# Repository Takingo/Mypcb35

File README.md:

# OmniCircuit AI

OmniCircuit AI is a local proof of concept for an autonomous PCB/PCBA design and manufacturing suite. The current implementation focuses on the ESP32-S3 + DWM3000 UWB Anchor example and establishes the architecture for:

- Parsing structured schematic, BOM, and PCB constraint inputs.
- Running deterministic engineering checks for RF, isolation, power, level shifting, expansion, and testability requirements.
- Producing AI design, validation, and manufacturing handoff reports.
- Presenting the project state in a Flutter dashboard.

The referenced `Corning-AI/PCBai` repository currently presents a public roadmap-style README for conversational PCB design, placement, routing, DRC, SI, and Gerber export. This workspace therefore treats PCBai as a planned adapter boundary while the local proof of concept supplies deterministic parsers and validators that can be connected to PCBai or KiCad automation later.

## Run the Local Engine

```powershell
python -m engine.run_pipeline --project-root .
```

Generated files are written to `outputs/uwb_anchor/` and the dashboard asset is written to `assets/generated/uwb_anchor_analysis.json`.

## Run the Flutter Dashboard

```powershell
C:\flutter\bin\flutter.bat pub get
C:\flutter\bin\flutter.bat run -d chrome
```

The input panel supports both manual text entry and file import. Use `Ister Dosyasi`, `BOM Yukle`, or `Teknik Not` to load text-based design inputs such as `.md`, `.csv`, `.txt`, `.json`, `.net`, `.xml`, `.yaml`, `.sch`, or `.kicad_sch` files directly into the matching field. On Windows desktop you can either browse with `Gozat` or paste a path such as `C:\Mypcb\BOM.csv` and press `Yoldan Yukle`.

## Project Layout

- `SCHEMATIC.md`, `BOM.csv`, `PCB_NOTES.md`: UWB anchor input package.
- `engine/`: Python proof-of-concept engine, including the Phase 2 KiCad automation bridge.
- `lib/`: Flutter dashboard.
- `assets/generated/`: Engine output consumed by Flutter.
- `outputs/`: Reports and manufacturing handoff placeholders.

## Phase 2 KiCad Bridge

The KiCad bridge lives in `engine/kicad_automation_service.py`. It reads `AI_Netlist_v1`, creates KiCad project artifacts, injects RF and AC safety constraints, and can run headless `kicad-cli` DRC/Gerber/drill/CPL exports when KiCad is installed.

```powershell
python -m engine.kicad_automation_service --netlist outputs/phase1/AI_NETLIST_V1.example.json --output-root outputs/kicad
```

On this Windows workspace with KiCad 10 installed, use the wrapper script:

```powershell
.\tool\run_kicad_phase2.ps1 -Export
```

For automation testing only, exports can be forced despite DRC violations:

```powershell
.\tool\run_kicad_phase2.ps1 -Export -ContinueOnDrcError
```

## Phase 3 DRC Feedback

KiCad DRC JSON can be normalized into `DRC_REPORT_V1` and converted into PCBai-style optimization penalties:

```powershell
& "C:\Program Files\KiCad\10.0\bin\python.exe" -m engine.drc_parser `
  --input outputs\kicad\esp32_s3_dwm3000_uwb_anchor_with_relay_outputs\manufacturing\drc_report.json `
  --output outputs\phase3\DRC_REPORT_V1.json
```

The Flutter dashboard includes a `DRC` tab that reads `assets/generated/drc_report_v1.json`.

## Phase 4 Closed-Loop Layout Optimization

The layout optimizer reads normalized DRC feedback, applies conservative `pcbnew` repairs, reruns DRC, and exports manufacturing files only when the final DRC count is zero.

```powershell
.\tool\run_layout_optimizer.ps1
```

Generated status:

- `outputs/phase4/layout_optimization_status.json`
- `outputs/phase4/gerber/`
- `outputs/phase4/drill/`
- `outputs/phase4/position/pick_and_place.csv`

Current KiCad status for the UWB anchor proof of concept:

- Schematic ERC: `0` violations.
- PCB DRC: `0` violations after closed-loop optimizer.
- Manufacturing exports: Gerber, drill, and pick-and-place generated.

## Simulation and PCBA Evidence

Run deterministic first-order engineering checks:

```powershell
.\tool\run_simulation_checks.ps1
```

Run assembly/PCBA visual exports:

```powershell
.\tool\run_pcba_exports.ps1
```

Generated files include:

- `outputs/simulation/simulation_report.json`
- `outputs/simulation/simulation_report.md`
- `outputs/assembly/*.pdf`
- `outputs/assembly/*.svg`
- `outputs/assembly/pcba_preview.glb`

## Fabrication Package

Create the local PCBWay/JLCPCB-style production archive and quote estimate:

```powershell
.\tool\run_fabrication_package.ps1
```

Generated package:

- `outputs/fabrication/Quantum_Mind_Anchor_v2_4_Production.zip`

## Engineering Readiness Gate

DRC=0 is not enough to claim a real production-ready electronic design. Run the engineering audit to verify schematic symbols/ERC evidence, active PCB consistency, simulation evidence, PCBA handoff files, and fabrication package integrity.

```powershell
.\tool\run_engineering_audit.ps1
```

Generated files:

- `outputs/engineering/engineering_readiness_report.json`
- `assets/generated/engineering_readiness_report.json`

Latest local audit result:

- `overall_status`: `review_required`
- `readiness_percent`: `86`
- blockers: `0`
- review warnings: `1` simulation/stackup review item

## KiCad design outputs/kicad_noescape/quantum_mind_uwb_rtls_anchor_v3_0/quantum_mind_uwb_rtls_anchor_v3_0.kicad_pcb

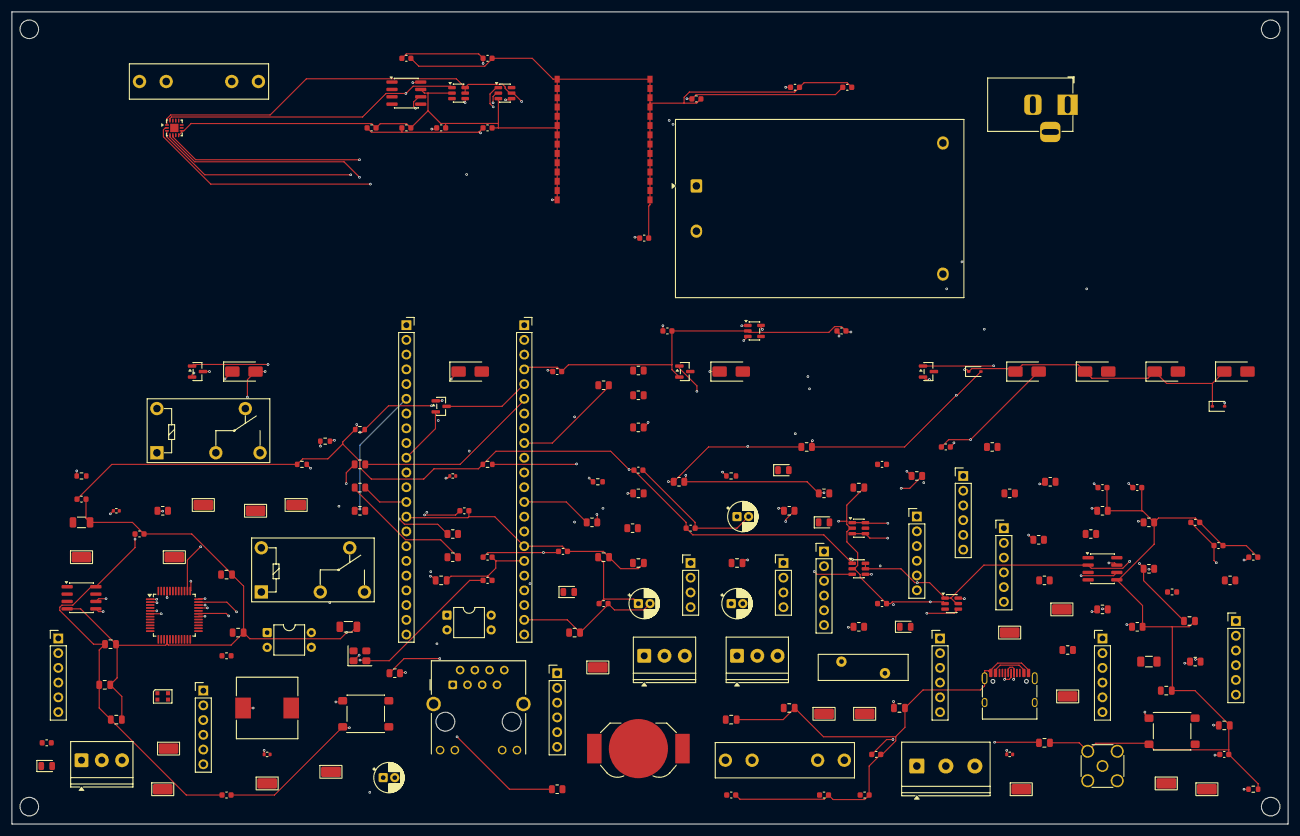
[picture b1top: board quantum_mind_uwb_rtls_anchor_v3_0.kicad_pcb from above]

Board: 4 copper layers, 220.0 x 140.0 mm, 195 parts (0 on the bottom side), 65 nets.

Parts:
ANT1: SMA Female Edge Mount 50Ω; SMA_Amphenol_132134_Vertical
BAT1: CR2032 Holder SMD; BatteryHolder_LINX_BAT-HLD-012-SMT
C1, C2, C3, C4: 10µF/50V Electrolytic; CP_Radial_D5.0mm_P2.00mm
C5, C6, C7, C8, C9, C10, C11, C12: 100nF/50V X7R 0805; C_0805_2012Metric
C13, C14, C15, C16: 10µF/16V X5R 0805; C_0805_2012Metric
C17, C18, C19, C20: 1µF/16V X7R 0603; C_0603_1608Metric
C21, C22: 22µF/10V X5R 1206; C_1206_3216Metric
C23, C24: 4.7µF/50V X7R 0805; C_0805_2012Metric
C25, C26: 10µF/6.3V X5R 0805; C_0805_2012Metric
C27, C28, C29, C30, C33, C34, C35, C36, C37, C38: 100nF/16V X7R 0603; C_0603_1608Metric
C31: 330pF/50V C0G 0603; C_0603_1608Metric
C32: 100pF/50V C0G 0603; C_0603_1608Metric
C39, C40, C41, C42: 100nF/50V X7R 0603; C_0603_1608Metric
C43, C44: 10µF/25V X5R 0805; C_0805_2012Metric
C90, C91, C92, C93, C94, C95, C96, C97, C98, C99, C100, C101, C102: 100nF; C_0603_1608Metric
C_X1A, C_X1A-C_X1B, C_X1B: 18pF/50V C0G 0603; C_0603_1608Metric
D1: SS34-E3/57T; D_SMA
D2, D3: 1N5819; D_SMA
D4, D5: 1N4148TR; D_SOD-323
D6, D7, D8: SMBJ3.3A; D_SMA
D9: SMBJ1.8A; D_SMA
D10: USBLC6-2SC6; SOT-23-6
F1: 0215001.MXP; Fuseholder_Littelfuse_100_series_5x20mm
F2: 0ZCJ0050FF2G; Fuse_1206_3216Metric
FB1, FB2, FB3: BLM18PG221SN1D; L_0603_1608Metric
J1_AC: Screw Terminal 3-pin 5.0mm; TerminalBlock_Phoenix_PT-1,5-3-5.0-H_1x03_P5.00mm_Horizontal
J1_USB: USB Type-C Receptacle 16-pin; USB_C_Receptacle_HRO_TYPE-C-31-M-12
J2: DC Power Jack 5.5×2.1mm; BarrelJack_Horizontal
J3, J4, J5: Screw Terminal 3-pin 3.5mm; TerminalBlock_Phoenix_PT-1,5-3-3.5-H_1x03_P3.50mm_Horizontal
J6, J7, J8, J9, J10, J11, J12, J13, J16, J17: Pin Header 1×6 2.54mm Male; PinHeader_1x06_P2.54mm_Vertical
J14, J15: Pin Header 1×4 2.54mm Male; PinHeader_1x04_P2.54mm_Vertical
J18: HR911105A; RJ45_Hanrun_HR911105A_Horizontal
J_FUSE: Fuse Holder 5×20mm PCB; Fuseholder_Littelfuse_100_series_5x20mm
K1, K2: G5Q-14-DC5; Relay_SPDT_Omron-G5Q-1
L1: CDRH104R-220NC; L_10.4x10.4_H4.8
LED1, LED5: Green LED 0805; LED_0805_2012Metric
LED2: Blue LED 0805; LED_0805_2012Metric
LED3: Red LED 0805; LED_0805_2012Metric
LED4: Yellow LED 0805; LED_0805_2012Metric
LED6: WS2812B-2020; LED_WS2812B-2020_PLCC4_2.0x2.0mm
Q1, Q2, Q3, Q4: 2N7002; SOT-23
R1, R1-R3R_LED4R_LED5, R2, R3: 220Ω 0805 1/4W; R_0805_2012Metric
R6, R7, R8, R9, R18, R19, R28, R29, R30, R34: 10kΩ 0805 1/4W; R_0805_2012Metric
R10, R11, R41, R42: 1kΩ 0805 1/4W; R_0805_2012Metric
R12, R13: 4.7kΩ 0805 1/4W; R_0805_2012Metric
R14: 10kΩ 0805 1%; R_0805_2012Metric
R15: 31.6kΩ 0805 1%; R_0805_2012Metric
R16, R17: 330Ω 0805 1/4W; R_0805_2012Metric
R20, R21, R22, R23, R31, R32: 100Ω 0805 1/4W; R_0805_2012Metric
R33: 0Ω 0805; R_0805_2012Metric
R35, R36, R37: 10kΩ 0603 1/8W; R_0603_1608Metric
R38, R39, R40: 100Ω 0603 1/8W; R_0603_1608Metric
R43, R44, R45, R46: 49.9Ω 0402 1%; R_0402_1005Metric
R47: 470Ω 0805 1/4W; R_0805_2012Metric
RV1: 14D471K; RV_Disc_D15.5mm_W4.5mm_P7.5mm
R_LED4, R_LED5: 220Ω 0805 1/4W; R_0805_2012Metric
R_RST1, R_RST2: 10kΩ 0603 1/8W; R_0603_1608Metric
R_WDG: 100kΩ 0805 1/4W; R_0805_2012Metric
SK1, SK2: PinSocket_1x22_P2.54mm; PinSocket_1x22_P2.54mm_Vertical
SW1, SW2: Tactile Switch 6×6mm SMD; SW_SPST_PTS645Sx43SMTR92
TP1, TP2, TP3, TP4, TP5, TP6, TP7, TP8, TP9, TP10, TP11, TP12, TP13, TP14, TP15, TP16, TP17, TP18: Test Point SMD 1.27mm Red; TestPoint_Keystone_5015_Micro_Mini
U2: DWM3000
U3: HLK-10M05; Converter_ACDC_Hi-Link_HLK-10Mxx
U4: TPS54331DR; SOIC-8_3.9x4.9mm_P1.27mm
U5: TPS780180200DRV; SOT-23-5
U6: TXB0104RGYR; WQFN-14-1EP_2.5x2.5mm_P0.5mm_EP1.45x1.45mm
U7, U13, U14: SN74LVC1T45DBVR; SOT-23-6
U8: TPL5010DDCR; SOT-23-6
U9: DS3231SN; SOIC-8_3.9x4.9mm_P1.27mm
U10: AT24C256C-SSHL; SOIC-8_3.9x4.9mm_P1.27mm
U11, U12: PC817X2CSP9F; DIP-4_W7.62mm
U15: W5500; LQFP-48_7x7mm_P0.5mm
X1: 25MHz / 18pF; Crystal_SMD_3225-4Pin_3.2x2.5mm

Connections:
1V8_DWM: C17.1, C18.1, C19.1, C20.1, C27.1, C28.1, C30.1, C33.1, C35.1, C38.1, D9.2, R35.1, R36.1, R37.1, U5.3, U6.14, U7.1, U13.1, U14.6
3V3_MAIN: C3.1, C4.1, C6.1, C7.1, C8.1, C9.1, C10.1, C23.1, C24.1, C29.1, C34.1, C36.1, C37.1, R28.1, R29.1, R30.1, R34.1, U5.1, U6.1, U7.5, U7.6, U8.5, U9.2, U10.8, U13.5, U13.6, U14.1, U14.5
5V_MAIN: C1.1, C2.1
5V_USB: J1_USB.A4, J1_USB.A9, J1_USB.B4, J1_USB.B9
5V_USB_FILTERED: SK1.1, SK2.1
+1V8: C92.1, C94.1, C96.1, C98.1, C102.1
+3V3: C90.1, C91.1, C93.1, C95.1, C97.1, C100.1, C101.1
+5V_ISO: C99.1, D1.1, D2.1, D3.1, D4.1, D5.1, D6.1, D7.1, D8.1, D9.1, K1.1, K2.1
AC_L: J1_AC.1, RV1.1, U3.1
AC_N: J1_AC.2, RV1.2, U3.2
GND: ANT1.2, C1.2, C2.2, C3.2, C4.2, C5.2, C6.2, C7.2, C8.2, C9.2, C10.2, C11.2, C12.2, C13.2, C14.2, C15.2, C16.2, C17.2, C18.2, C19.2, C20.2, C21.2, C22.2, C23.2, C24.2, C25.2, C26.2, C27.2, C28.2, C29.2, C30.2, C31.2, C32.2, C33.2, C34.2, C35.2, C36.2, C37.2, C38.2, C39.2, C40.2, C41.2, C42.2, C43.2, C44.2, C90.2, C91.2, C92.2, C93.2, C94.2, C95.2, C96.2, C97.2, C98.2, C99.2, C100.2, C101.2, C102.2, C_X1A.2, C_X1B.2, D10.2, J1_USB.A1, J1_USB.A12, J1_USB.B1, J1_USB.B12, J1_USB.SH, J2.2, J2.3, J18.SH, Q1.2, Q2.2, Q3.2, Q4.2, R14.2, R18.2, R19.2, R_RST2.2, R_WDG.2, SK1.2, SK1.10, SK1.11, SK1.13, SK1.14, SK2.2, SK2.3, SK2.4, SK2.16, SK2.17, SK2.18, SK2.19, SK2.20, SK2.21, SK2.22, SW1.2, SW2.2, U2.1, U2.2, U2.3, U2.4, U2.5, U2.6, U2.7, U2.8, U2.9, U2.10, U2.11, U2.12, U2.13, U2.14, U2.15, U2.16, U2.17, U2.18, U2.19, U2.20, U2.21, U2.22, U2.23, U2.24, U2.25, U2.26, U2.27, U2.28, U3.4, U4.7, U5.2, U6.7, U6.8, U7.2, U8.3, U9.5, U10.4, U13.2, U14.2, U15.16
NET_DWM3000_DEBUGOUT_1V8: R37.2, R40.1
NET_DWM3000_EXT_RX_1V8: R35.2, U14.4
NET_DWM3000_EXT_TX_1V8_SERIES: R36.2, R39.1, U13.3
NET_DWM3000_RSTN_1V65: R_RST1.2, R_RST2.1
NET_DWM3000_SPI_CLK_3V3_SERIES: R20.2, U6.2
NET_DWM3000_SPI_CS_3V3_SERIES: R23.2, U6.5
NET_DWM3000_SPI_MISO_3V3_SERIES: R22.2, U6.4
NET_DWM3000_SPI_MOSI_3V3_SERIES: R21.2, U6.3
NET_ESP32_EN: D5.2, Q1.3, R28.2, R47.1, SK1.3, SW1.1, U8.4
NET_ESP32_EXT_RX: R38.1, SK1.9
NET_ESP32_EXT_TX: SK1.8, U13.4
NET_ESP32_GPIO0: D4.2, Q2.3, R29.2, SK2.5, SW2.1
NET_ESP32_GPIO1: R_LED4.1, SK1.17
NET_ESP32_GPIO2: R_LED5.1, SK1.18
NET_ESP32_GPIO4: R16.1, SK1.4
NET_ESP32_GPIO5: R17.1, SK1.5
NET_ESP32_GPIO6: R2.1, SK1.6
NET_ESP32_GPIO7: R3.1, SK1.7
NET_ESP32_GPIO8: C11.1, SK1.12
NET_ESP32_GPIO9: R_RST1.1, SK2.15
NET_ESP32_GPIO45: R30.2, SK2.6, U8.2
NET_ESP32_IRQ: SK2.10, U7.4
NET_ESP32_SPI_CLK: R20.1, SK2.14
NET_ESP32_SPI_CS: R23.1, SK2.11
NET_ESP32_SPI_MISO: R22.1, SK2.12
NET_ESP32_SPI_MOSI: R21.1, SK2.13
NET_I2C_SCL: R13.2, U9.7, U10.6
NET_I2C_SDA: R12.2, SK2.9, U9.6, U10.5
NET_U4_COMP: C31.1, C32.1, U4.6
NET_U4_FB: R14.1, R15.2
NET_U4_SW: D1.2, L1.1, U4.8
NET_U5_EN: R34.2, U5.5
NET_U8_DELAY: R_WDG.1, U8.1
NET_U11_COLLECTOR: Q3.1, R18.1
NET_U12_COLLECTOR: Q4.1, R19.1
NET_USB_DTR: Q1.1, R31.1
NET_USB_D_N: D10.3, D10.4, J1_USB.A7, J1_USB.B7
NET_USB_D_P: D10.1, D10.6, J1_USB.A6, J1_USB.B6
NET_USB_RTS: Q2.1, R32.1
NET_W5500_INT: R42.1, SK2.7
NET_W5500_INTn: R42.2, U15.38
NET_W5500_REGD: C44.1, U15.45
NET_W5500_RST: R41.1, SK2.8
NET_W5500_RX_N: J18.6, R46.1, U15.6
NET_W5500_RX_P: J18.3, R45.1, U15.5
NET_W5500_SPI2_CLK: SK1.22, U15.35
NET_W5500_SPI2_CS: SK1.19, U15.36
NET_W5500_SPI2_MISO: SK1.20, U15.34
NET_W5500_SPI2_MOSI: SK1.21, U15.33
NET_W5500_TX_N: J18.2, R44.1, U15.1
NET_W5500_TX_P: J18.1, R43.1, U15.2
NET_W5500_XTAL_IN: C_X1A.1, U15.30, X1.1
NET_W5500_XTAL_OUT: C_X1B.1, U15.31, X1.2
NET_W5500_nRESET: R41.2, U15.37

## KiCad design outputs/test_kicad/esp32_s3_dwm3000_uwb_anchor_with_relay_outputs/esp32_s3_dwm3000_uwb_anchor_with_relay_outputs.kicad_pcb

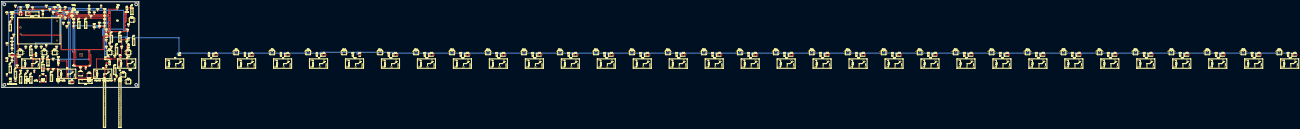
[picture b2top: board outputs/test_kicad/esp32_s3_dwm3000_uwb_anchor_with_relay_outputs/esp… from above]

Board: 4 copper layers, 160.0 x 100.0 mm, 323 parts (0 on the bottom side), 47 nets.

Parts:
ANT1: SMA_EDGE; Generic_SMD_2pin
BAT1: CR2032; Generic_SMD_2pin
C1, C2, C3, C4: 10uF/50V; C_0805_2012Metric
C5, C6, C7, C8, C9, C10, C11, C12, C39, C40, C41, C42: 100nF/50V; C_0805_2012Metric
C13, C14, C15, C16: 10uF/16V; C_0805_2012Metric
C17, C18, C19, C20: 1uF/16V; C_0805_2012Metric
C21, C22: 22uF/10V; C_0805_2012Metric
C23, C24: 4.7uF/50V; C_0805_2012Metric
C25, C26: 10uF/6.3V; C_0805_2012Metric
C27, C28, C29, C30, C33, C34, C35, C36, C37, C38: 100nF/16V; C_0805_2012Metric
C31: 330pF/50V; C_0805_2012Metric
C32: 100pF/50V; C_0805_2012Metric
C43, C44: 10uF/25V; C_0805_2012Metric
C90, C91, C92, C93, C94, C95, C96, C97, C98, C99, C100, C101, C102, C103, C104: 100nF; C_0805_2012Metric
D1: SS34-E3/57T; D_SMA
D2, D3: 1N5819; D_SMA
D4, D5: 1N4148TR; D_SOD-323
D6, D7, D8: SMBJ3.3A; D_SMA
D9: SMBJ1.8A; D_SMA
D10: USBLC6-2SC6; SOT-23-6
D11, D12, D13, D14, D15, D16, D17, D18, D19, D20, D21, D22, D23, D24, D25, D26, D27, D28, D29, D30, D31, D32, D33, D34, D35, D36: SS14; D_SMA
F1: 0215001.MXP; Fuse_1206_3216Metric
F2: 0ZCJ0050FF2G; Fuse_1206_3216Metric
FB1, FB2, FB3: BLM18PG221SN1D; Generic_SMD_2pin
J1: TYPE-C-31-M-12; PinHeader_1x04_P2.54mm_Vertical
J2: PJ-002A; PinHeader_1x04_P2.54mm_Vertical
J3, J4, J5: KF350-3P; PinHeader_1x04_P2.54mm_Vertical
J6, J7, J8, J9, J10, J11, J12, J13, J16, J17: Header 1x6; PinHeader_1x04_P2.54mm_Vertical
J14, J15: Header 1x4; PinHeader_1x04_P2.54mm_Vertical
J18: RJ45_MAG; PinHeader_1x04_P2.54mm_Vertical
J_FUSE: 01000063Z; Generic_SMD_2pin
K1, K2: G5Q-14-DC5; Relay_SPDT_Omron-G5Q-1
K3, K4, K5, K6, K7, K8, K9, K10, K11, K12, K13, K14, K15, K16, K17, K18, K19, K20, K21, K22, K23, K24, K25, K26, K27, K28, K29, K30, K31, K32, K33, K34, K35, K36: 5V relay; Relay_SPDT_Omron-G5Q-1
L1: CDRH104R-220NC; Generic_SMD_2pin
LED1, LED2, LED3, LED4, LED5: LED 0805; Generic_SMD_2pin
LED6: WS2812B-2020; Generic_SMD_2pin
MOV1: 471VAC MOV; RV_Disc_D15.5mm_W4.5mm_P7.5mm
OK1, OK2, OK3, OK4, OK5, OK6, OK7, OK8, OK9, OK10, OK11, OK12, OK13, OK14, OK15, OK16, OK17, OK18, OK19, OK20, OK21, OK22, OK23, OK24, OK25, OK26, OK27, OK28, OK29, OK30, OK31, OK32, OK33, OK34, OK35, OK36: PC817; DIP-4_W7.62mm
Q1, Q2, Q3, Q4, Q5, Q6, Q7, Q8, Q9, Q10, Q11, Q12, Q13, Q14, Q15, Q16, Q17, Q18, Q19, Q20, Q21, Q22, Q23, Q24, Q25, Q26, Q27, Q28, Q29, Q30, Q31, Q32, Q33, Q34, Q35, Q36: 2N7002; SOT-23
R1, R2, R3, R4, R5: 220Ohm; R_0805_2012Metric
R6, R7, R8, R9, R14, R18, R19, R28, R29, R30, R34, R35, R36, R37: 10kΩ; R_0805_2012Metric
R10, R11, R41, R42: 1kΩ; R_0805_2012Metric
R12, R13: 4.7kΩ; R_0805_2012Metric
R15: 31.6kΩ; R_0805_2012Metric
R16, R17: 330Ohm; R_0805_2012Metric
R20, R21, R22, R23, R24, R25, R26, R27, R31, R32, R38, R39, R40: 100Ohm; R_0805_2012Metric
R33: 0Ohm; R_0805_2012Metric
R43, R44, R45, R46: 49.9Ohm; R_0805_2012Metric
R47: 470Ohm; R_0805_2012Metric
RV1: 14D471K; RV_Disc_D15.5mm_W4.5mm_P7.5mm
SK1, SK2: Female_Header_1x22_2.54mm; PinSocket_1x22_P2.54mm_Vertical
SW1, SW2: 6x6mm; Generic_SMD_2pin
TP1, TP2, TP3, TP4, TP5, TP6, TP7, TP8, TP9, TP10, TP11, TP12, TP13, TP14, TP15, TP16, TP17, TP18: Test Point SMD; Generic_SMD_2pin
U1: ESP32-S3-WROOM-2-N32R16; ESP32-S3-WROOM-2
U2: DWM3000
U3: HLK-10M05; Converter_ACDC_Hi-Link_HLK-10Mxx
U4: TPS54331DR; SOIC-8_3.9x4.9mm_P1.27mm
U5: TPS780180200DRV; SOT-23-5
U6: TXB0104RGYR; WQFN-14-1EP_2.5x2.5mm_P0.5mm_EP1.45x1.45mm
U7, U13, U14: SN74LVC1T45DBVR; SOT-23-5
U8: TPL5010DDCR; SOT-23-6
U9: DS3231SN; SOIC-8_3.9x4.9mm_P1.27mm
U10: AT24C256C-SSHL; SOIC-8_3.9x4.9mm_P1.27mm
U11, U12: PC817X2CSP9F; DIP-4_W7.62mm
U15: W5500; LQFP-48_7x7mm_P0.5mm
X1: 25MHz Crystal; Generic_SMD_2pin

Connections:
+1V8: C92.1, C94.1, C96.1, C98.1, C100.1, C104.1, U2.2, U4.6, U8.3
+3V3: C90.1, C91.1, C93.1, C95.1, C97.1, C99.1, C102.1, C103.1, U1.2, U1.3, U3.1, U4.1, U5.1, U8.1, U8.5
+5V_ISO: C101.1, D1.1, D2.1, D3.1, D4.1, D5.1, D6.1, D7.1, D8.1, D9.1, D10.1, D11.1, D12.1, D13.1, D14.1, D15.1, D16.1, D17.1, D18.1, D19.1, D20.1, D21.1, D22.1, D23.1, D24.1, D25.1, D26.1, D27.1, D28.1, D29.1, D30.1, D31.1, D32.1, D33.1, D34.1, D35.1, D36.1, K1.1, K2.1, K3.1, K4.1, K5.1, K6.1, K7.1, K8.1, K9.1, K10.1, K11.1, K12.1, K13.1, K14.1, K15.1, K16.1, K17.1, K18.1, K19.1, K20.1, K21.1, K22.1, K23.1, K24.1, K25.1, K26.1, K27.1, K28.1, K29.1, K30.1, K31.1, K32.1, K33.1, K34.1, K35.1, K36.1, U6.3, U7.2, U7.3
AC_L_PROTECTED: F1.1, J1.1, MOV1.1, U6.1
DWM_EXT_TX_1V8: U2.9, U5.4
DWM_EXT_TX_3V3: U1.8, U5.3
DWM_IRQ_1V8: U2.8, U4.4
DWM_IRQ_3V3: U1.32, U4.3
GND: C90.2, C91.2, C92.2, C93.2, C94.2, C95.2, C96.2, C97.2, C98.2, C99.2, C100.2, C101.2, C102.2, C103.2, C104.2, J2.2, J2.3, J2.4, OK1.2, OK2.2, OK3.2, OK4.2, OK5.2, OK6.2, OK7.2, OK8.2, OK9.2, OK10.2, OK11.2, OK12.2, OK13.2, OK14.2, OK15.2, OK16.2, OK17.2, OK18.2, OK19.2, OK20.2, OK21.2, OK22.2, OK23.2, OK24.2, OK25.2, OK26.2, OK27.2, OK28.2, OK29.2, OK30.2, OK31.2, OK32.2, OK33.2, OK34.2, OK35.2, OK36.2, Q1.2, Q2.2, Q3.2, Q4.2, Q5.2, Q6.2, Q7.2, Q8.2, Q9.2, Q10.2, Q11.2, Q12.2, Q13.2, Q14.2, Q15.2, Q16.2, Q17.2, Q18.2, Q19.2, Q20.2, Q21.2, Q22.2, Q23.2, Q24.2, Q25.2, Q26.2, Q27.2, Q28.2, Q29.2, Q30.2, Q31.2, Q32.2, Q33.2, Q34.2, Q35.2, Q36.2, R41.2, R42.2, U1.1, U1.39, U1.40, U1.41, U2.1, U2.4, U2.5, U2.6, U2.7, U2.10, U2.11, U2.12, U2.13, U2.14, U2.15, U2.16, U2.17, U2.18, U2.19, U2.20, U2.21, U2.22, U2.24, U2.25, U2.26, U2.27, U2.28, U4.2, U4.5, U5.2, U5.5, U6.4, U8.2
RELAY1_DRIVE: K1.2, Q1.1, U1.31
RELAY2_DRIVE: K2.2, Q2.1
RELAY3_DRIVE: K3.2, Q3.1
RELAY4_DRIVE: K4.2, Q4.1
RELAY5_DRIVE: K5.2, Q5.1
RELAY6_DRIVE: K6.2, Q6.1
RELAY7_DRIVE: K7.2, Q7.1
RELAY8_DRIVE: K8.2, Q8.1
RELAY9_DRIVE: K9.2, Q9.1
RELAY10_DRIVE: K10.2, Q10.1
RELAY11_DRIVE: K11.2, Q11.1
RELAY12_DRIVE: K12.2, Q12.1
RELAY13_DRIVE: K13.2, Q13.1
RELAY14_DRIVE: K14.2, Q14.1
RELAY15_DRIVE: K15.2, Q15.1, U1.26
RELAY16_DRIVE: K16.2, Q16.1, U1.25
RELAY17_DRIVE: K17.2, Q17.1, U1.24
RELAY18_DRIVE: K18.2, Q18.1, U1.23
RELAY19_DRIVE: K19.2, Q19.1, U1.22
RELAY20_DRIVE: K20.2, Q20.1, U1.21
RELAY21_DRIVE: K21.2, Q21.1, U1.20
RELAY22_DRIVE: K22.2, Q22.1, U1.19
RELAY23_DRIVE: K23.2, Q23.1, U1.16
RELAY24_DRIVE: K24.2, Q24.1, U1.15
RELAY25_DRIVE: K25.2, Q25.1, U1.28
RELAY26_DRIVE: K26.2, Q26.1
RELAY27_DRIVE: K27.2, Q27.1, U1.30
RELAY28_DRIVE: K28.2, Q28.1, U1.29
RELAY29_DRIVE: K29.2, Q29.1
RELAY30_DRIVE: K30.2, Q30.1
RELAY31_DRIVE: K31.2, Q31.1
RELAY32_DRIVE: K32.2, Q32.1
RELAY33_DRIVE: K33.2, Q33.1
RELAY34_DRIVE: K34.2, Q34.1
RELAY35_DRIVE: K35.2, Q35.1
RELAY36_DRIVE: K36.2, Q36.1
SPI_CS_3V3: R10.1, R10.2, U1.36, U3.2
UWB_RF_50R: J2.1, U2.23

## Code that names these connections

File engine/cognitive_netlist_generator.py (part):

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        )
        nets.extend(
            [
                NetConnection("SPI_CS_3V3",   ["U1.GPIO10", "R20.1", "R20.2", "U6.A1"], "spi_3v3", "ESP32 SPI chip select through source resistor."),
                NetConnection("SPI_MOSI_3V3",  ["U1.GPIO11", "R21.1", "R21.2", "U6.A2"], "spi_3v3", "ESP32 SPI MOSI through source resistor."),
                NetConnection("SPI_CLK_3V3",   ["U1.GPIO12", "R22.1", "R22.2", "U6.A3"], "spi_3v3", "ESP32 SPI clock through source resistor."),
                NetConnection("SPI_MISO_3V3",  ["U1.GPIO13", "R23.1", "R23.2", "U6.A4"], "spi_3v3", "ESP32 SPI MISO through source resistor."),
                NetConnection("SPI_CS_1V8",    ["U6.B1", "U2.SPI_CS"],   "spi_1v8", "Translated DWM3000 SPI CS."),
                NetConnection("SPI_MOSI_1V8",  ["U6.B2", "U2.SPI_MOSI"], "spi_1v8", "Translated DWM3000 SPI MOSI."),
                NetConnection("SPI_CLK_1V8",   ["U6.B3", "U2.SPI_CLK"],  "spi_1v8", "Translated DWM3000 SPI CLK."),
                NetConnection("SPI_MISO_1V8",  ["U6.B4", "U2.SPI_MISO"], "spi_1v8", "Translated DWM3000 SPI MISO."),
                NetConnection("DWM_IRQ_3V3",   ["U7.B", "U1.GPIO14"],    "rtls_3v3", "IRQ translated to ESP32 domain."),
                NetConnection("DWM_IRQ_1V8",   ["U7.A", "U2.IRQ"],       "rtls_1v8", "IRQ source from DWM3000 domain."),
                NetConnection("DWM_EXTTX_3V3", ["U13.B", "U1.GPIO15"],   "rtls_3v3", "EXT_TX translated to ESP32."),
                NetConnection("DWM_EXTTX_1V8", ["U13.A", "U2.EXT_TX"],   "rtls_1v8", "EXT_TX source DWM3000."),
                NetConnection("DWM_EXTRX_3V3", ["U14.A", "U1.GPIO16"],   "rtls_3v3", "EXT_RX from ESP32."),
                NetConnection("DWM_EXTRX_1V8", ["U14.B", "U2.EXT_RX"],   "rtls_1v8", "EXT_RX to DWM3000."),
            ]
        )
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        rules: list,
        reasoning: list,
    ) -> None:
        nets.append(NetConnection("UWB_RF_50R", ["U2.RF_PIN23", "J2.CENTER"], "rf_50r", "DWM3000 RF output to SMA antenna connector."))
        rules.extend(
            [
                DesignRule("RF_50R_WIDTH_035MM", "error", "RF trace must be 50 ohm controlled impedance with 0.35mm width on specified FR4 stackup.", ["UWB_RF_50R"]),
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
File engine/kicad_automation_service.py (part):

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            elif "CENTER" in pins and ({"GND", "SHIELD"} & pins):
                value = "SMA Anten Konektörü"
                comp_type = "sma_connector"
            elif {"L", "N", "PE", "AC_L", "AC_N", "EARTH"} & pins:
                value = "AC Şebeke Girişi"
                comp_type = "ac_connector"
            else:
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
    def _inject_rf_rule_metadata(self, board: Any) -> None:
        comments = [
            "RF kural: UWB_RF_50R, DWM3000 pin 23 → SMA, 50 Ohm, 0.35mm genişlik.",
            "RF kural: Anten trasesi üzerinde via, test noktası, bileşen yok; 3mm keepout zorunlu.",
        ]
        tb = board.GetTitleBlock() if hasattr(board, "GetTitleBlock") else None
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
